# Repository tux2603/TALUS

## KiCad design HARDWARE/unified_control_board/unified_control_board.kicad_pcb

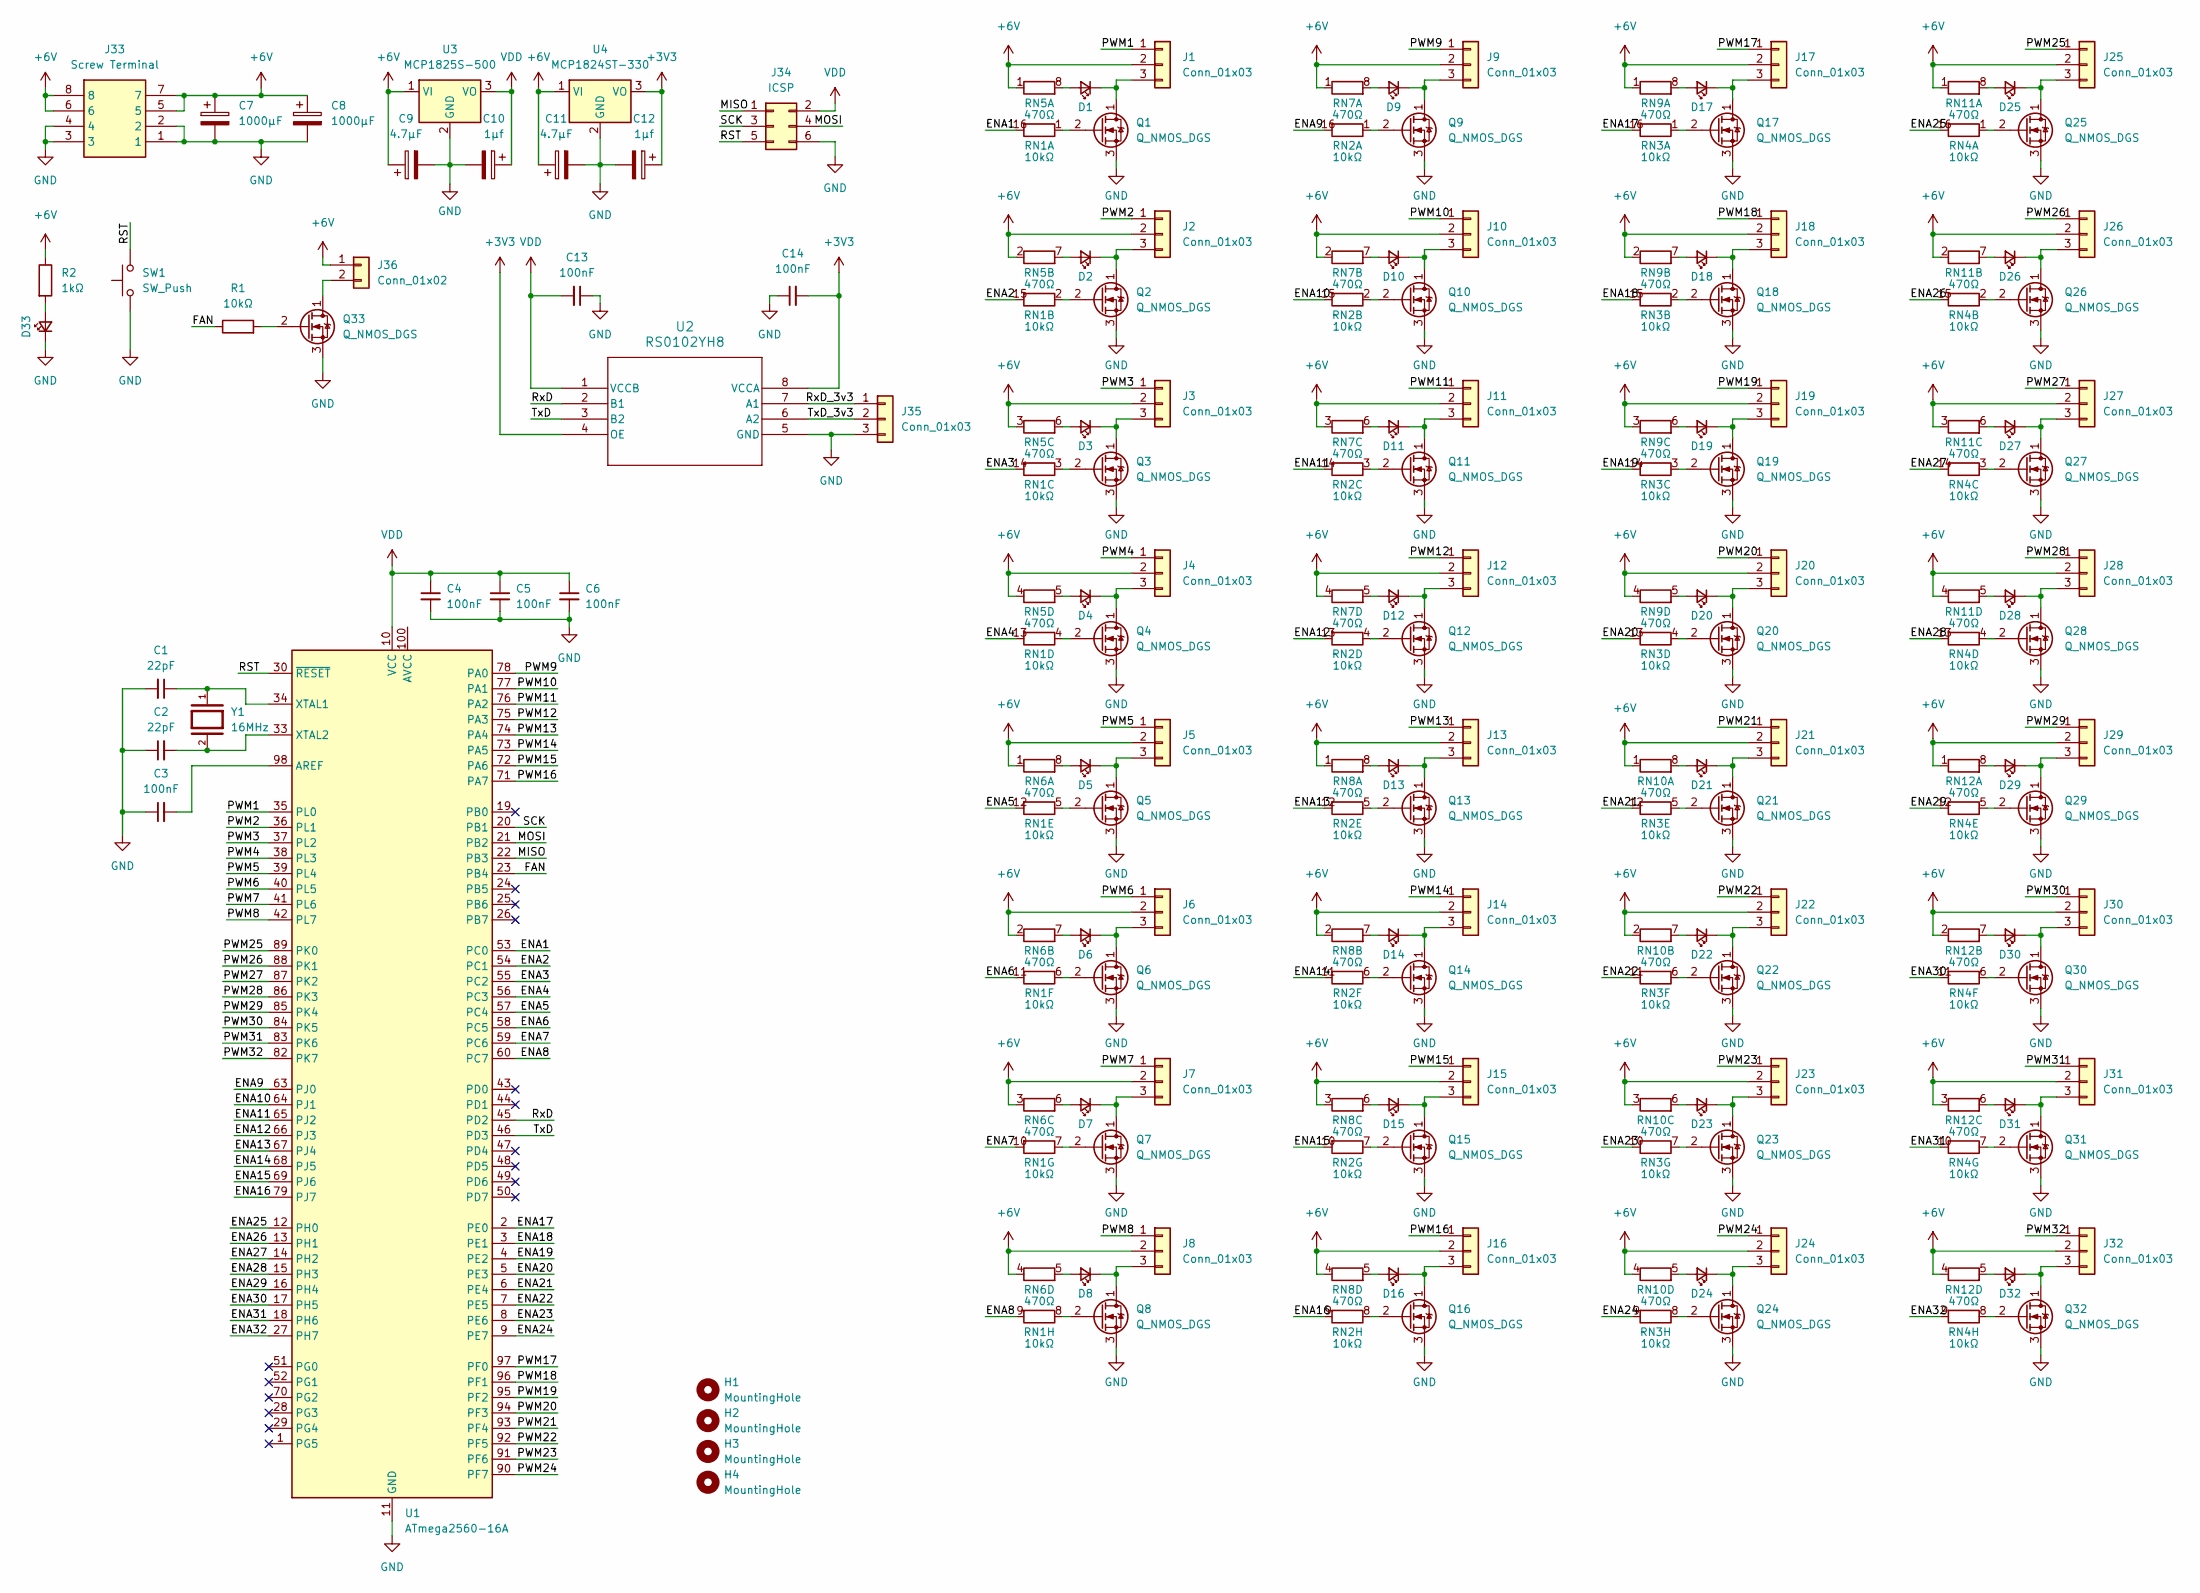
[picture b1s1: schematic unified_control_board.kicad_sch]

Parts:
C1, C2: 22pF; C_0603_1608Metric
C3, C4, C5, C6, C13, C14: 100nF; C_0805_2012Metric
C7, C8: 1000µF; CP_Radial_D10.0mm_P5.00mm
C9, C11: 4.7µF; CP_Elec_4x4.5
C10, C12: 1µf; CP_Elec_4x4.5
D1, D2, D3, D4, D5, D6, D7, D8, D9, D10, D11, D12, D13, D14, D15, D16, D17, D18, D19, D20, D21, D22, D23, D24, D25, D26, D27, D28, D29, D30, D31, D32, D33: Red; LED_0805_2012Metric
H1, H2, H3, H4: MountingHole; MountingHole_2.2mm_M2
J1, J2, J3, J4, J5, J6, J7, J8, J9, J10, J11, J12, J13, J14, J15, J16, J17, J18, J19, J20, J21, J22, J23, J24, J25, J26, J27, J28, J29, J30, J31, J32, J35: Conn_01x03; PinHeader_1x03_P2.54mm_Vertical
J33: Screw Terminal; 399200302; Mouser Part Number 538-39920-0302
J34: ICSP; PinHeader_2x03_P2.54mm_Vertical
J36: Conn_01x02; PinHeader_1x02_P2.54mm_Vertical
Q1, Q2, Q3, Q4, Q5, Q6, Q7, Q8, Q9, Q10, Q11, Q12, Q13, Q14, Q15, Q16, Q17, Q18, Q19, Q20, Q21, Q22, Q23, Q24, Q25, Q26, Q27, Q28, Q29, Q30, Q31, Q32, Q33: Q_NMOS_DGS; SOIC-8_3.9x4.9mm_P1.27mm
R1: 10kΩ; R_0805_2012Metric
R2: 1kΩ; R_0805_2012Metric
RN1, RN2, RN3, RN4: 10kΩ; R_Array_Convex_8x0602
RN5, RN6, RN7, RN8, RN9, RN10, RN11, RN12: 470Ω; R_Array_Convex_4x0603
SW1: SW_Push; SW_PTS647SM38SMTR2LFS_CNK
U1: ATmega2560-16A; TQFP-100_14x14mm_P0.5mm
U2: RS0102YH8; SOT-8-RS0102YH8_JRT
U3: MCP1825S-500; SOT-223-3_TabPin2
U4: MCP1824ST-330; SOT-223-3_TabPin2
Y1: 16MHz; CRYSTAL_HC49SDLF_FXT; PARTREV 11.15.2016; DigiKey_Part_Number 535-9875-2-ND

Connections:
+3V3: C12.1, C14.2, U2.4 (OE), U2.8 (VCCA), U4.3 (VO)
+6V: C7.1, C8.1, C9.1, C11.1, J1.2, J2.2, J3.2, J4.2, J5.2, J6.2, J7.2, J8.2, J9.2, J10.2, J11.2, J12.2, J13.2, J14.2, J15.2, J16.2, J17.2, J18.2, J19.2, J20.2, J21.2, J22.2, J23.2, J24.2, J25.2, J26.2, J27.2, J28.2, J29.2, J30.2, J31.2, J32.2, J33.5, J33.6, J33.7, J33.8, J36.1, R2.1, RN5.1 (R1.1), RN5.2 (R2.1), RN5.3 (R3.1), RN5.4 (R4.1), RN6.1 (R1.1), RN6.2 (R2.1), RN6.3 (R3.1), RN6.4 (R4.1), RN7.1 (R1.1), RN7.2 (R2.1), RN7.3 (R3.1), RN7.4 (R4.1), RN8.1 (R1.1), RN8.2 (R2.1), RN8.3 (R3.1), RN8.4 (R4.1), RN9.1 (R1.1), RN9.2 (R2.1), RN9.3 (R3.1), RN9.4 (R4.1), RN10.1 (R1.1), RN10.2 (R2.1), RN10.3 (R3.1), RN10.4 (R4.1), RN11.1 (R1.1), RN11.2 (R2.1), RN11.3 (R3.1), RN11.4 (R4.1), RN12.1 (R1.1), RN12.2 (R2.1), RN12.3 (R3.1), RN12.4 (R4.1), U3.1 (VI), U4.1 (VI)
/ENA1: RN1.16 (R1.2), U1.53 (PC0)
/ENA2: RN1.15 (R2.2), U1.54 (PC1)
/ENA3: RN1.14 (R3.2), U1.55 (PC2)
/ENA4: RN1.13 (R4.2), U1.56 (PC3)
/ENA5: RN1.12 (R5.2), U1.57 (PC4)
/ENA6: RN1.11 (R6.2), U1.58 (PC5)
/ENA7: RN1.10 (R7.2), U1.59 (PC6)
/ENA8: RN1.9 (R8.2), U1.60 (PC7)
/ENA9: RN2.16 (R1.2), U1.63 (PJ0)
/ENA10: RN2.15 (R2.2), U1.64 (PJ1)
/ENA11: RN2.14 (R3.2), U1.65 (PJ2)
/ENA12: RN2.13 (R4.2), U1.66 (PJ3)
/ENA13: RN2.12 (R5.2), U1.67 (PJ4)
/ENA14: RN2.11 (R6.2), U1.68 (PJ5)
/ENA15: RN2.10 (R7.2), U1.69 (PJ6)
/ENA16: RN2.9 (R8.2), U1.79 (PJ7)
/ENA17: RN3.16 (R1.2), U1.2 (PE0)
/ENA18: RN3.15 (R2.2), U1.3 (PE1)
/ENA19: RN3.14 (R3.2), U1.4 (PE2)
/ENA20: RN3.13 (R4.2), U1.5 (PE3)
/ENA21: RN3.12 (R5.2), U1.6 (PE4)
/ENA22: RN3.11 (R6.2), U1.7 (PE5)
/ENA23: RN3.10 (R7.2), U1.8 (PE6)
/ENA24: RN3.9 (R8.2), U1.9 (PE7)
/ENA25: RN4.16 (R1.2), U1.12 (PH0)
/ENA26: RN4.15 (R2.2), U1.13 (PH1)
/ENA27: RN4.14 (R3.2), U1.14 (PH2)
/ENA28: RN4.13 (R4.2), U1.15 (PH3)
/ENA29: RN4.12 (R5.2), U1.16 (PH4)
/ENA30: RN4.11 (R6.2), U1.17 (PH5)
/ENA31: RN4.10 (R7.2), U1.18 (PH6)
/ENA32: RN4.9 (R8.2), U1.27 (PH7)
/FAN: R1.1, U1.23 (PB4)
/MISO: J34.1, U1.22 (PB3)
/MOSI: J34.4, U1.21 (PB2)
/PWM1: J1.1, U1.35 (PL0)
/PWM2: J2.1, U1.36 (PL1)
/PWM3: J3.1, U1.37 (PL2)
/PWM4: J4.1, U1.38 (PL3)
/PWM5: J5.1, U1.39 (PL4)
/PWM6: J6.1, U1.40 (PL5)
/PWM7: J7.1, U1.41 (PL6)
/PWM8: J8.1, U1.42 (PL7)
/PWM9: J9.1, U1.78 (PA0)
/PWM10: J10.1, U1.77 (PA1)
/PWM11: J11.1, U1.76 (PA2)
/PWM12: J12.1, U1.75 (PA3)
/PWM13: J13.1, U1.74 (PA4)
/PWM14: J14.1, U1.73 (PA5)
/PWM15: J15.1, U1.72 (PA6)
/PWM16: J16.1, U1.71 (PA7)
/PWM17: J17.1, U1.97 (PF0)
/PWM18: J18.1, U1.96 (PF1)
/PWM19: J19.1, U1.95 (PF2)
/PWM20: J20.1, U1.94 (PF3)
/PWM21: J21.1, U1.93 (PF4)
/PWM22: J22.1, U1.92 (PF5)
/PWM23: J23.1, U1.91 (PF6)
/PWM24: J24.1, U1.90 (PF7)
/PWM25: J25.1, U1.89 (PK0)
/PWM26: J26.1, U1.88 (PK1)
/PWM27: J27.1, U1.87 (PK2)
/PWM28: J28.1, U1.86 (PK3)
/PWM29: J29.1, U1.85 (PK4)
/PWM30: J30.1, U1.84 (PK5)
/PWM31: J31.1, U1.83 (PK6)
/PWM32: J32.1, U1.82 (PK7)
/RST: J34.5, SW1.2, U1.30 (~RESET)
/RxD: U1.45 (PD2), U2.2 (B1)
/RxD_3v3: J35.1, U2.7 (A1)
/SCK: J34.3, U1.20 (PB1)
/TxD: U1.46 (PD3), U2.3 (B2)
/TxD_3v3: J35.2, U2.6 (A2)
GND: C1.2, C2.1, C3.1, C4.2, C5.2, C6.2, C7.2, C8.2, C9.2, C10.2, C11.2, C12.2, C13.1, C14.1, D33.1 (K), J33.1, J33.2, J33.3, J33.4, J34.6, J35.3, Q1.3 (S), Q2.3 (S), Q3.3 (S), Q4.3 (S), Q5.3 (S), Q6.3 (S), Q7.3 (S), Q8.3 (S), Q9.3 (S), Q10.3 (S), Q11.3 (S), Q12.3 (S), Q13.3 (S), Q14.3 (S), Q15.3 (S), Q16.3 (S), Q17.3 (S), Q18.3 (S), Q19.3 (S), Q20.3 (S), Q21.3 (S), Q22.3 (S), Q23.3 (S), Q24.3 (S), Q25.3 (S), Q26.3 (S), Q27.3 (S), Q28.3 (S), Q29.3 (S), Q30.3 (S), Q31.3 (S), Q32.3 (S), Q33.3 (S), SW1.1, U1.11 (GND), U1.32 (GND), U1.62 (GND), U1.81 (GND), U1.99 (GND), U2.5 (GND), U3.2 (GND), U4.2 (GND)
unnamed: D1.2 (A), RN5.8 (R1.2)
unnamed: D1.1 (K), J1.3, Q1.1 (D)
unnamed: D2.2 (A), RN5.7 (R2.2)
unnamed: D2.1 (K), J2.3, Q2.1 (D)
unnamed: D3.2 (A), RN5.6 (R3.2)
unnamed: D3.1 (K), J3.3, Q3.1 (D)
unnamed: D4.2 (A), RN5.5 (R4.2)
unnamed: D4.1 (K), J4.3, Q4.1 (D)
unnamed: D5.2 (A), RN6.8 (R1.2)
unnamed: D5.1 (K), J5.3, Q5.1 (D)
unnamed: D6.2 (A), RN6.7 (R2.2)
unnamed: D6.1 (K), J6.3, Q6.1 (D)
unnamed: D7.2 (A), RN6.6 (R3.2)
unnamed: D7.1 (K), J7.3, Q7.1 (D)
unnamed: D8.2 (A), RN6.5 (R4.2)
unnamed: D8.1 (K), J8.3, Q8.1 (D)
unnamed: D9.2 (A), RN7.8 (R1.2)
unnamed: D9.1 (K), J9.3, Q9.1 (D)
unnamed: D10.2 (A), RN7.7 (R2.2)
unnamed: D10.1 (K), J10.3, Q10.1 (D)
unnamed: D11.2 (A), RN7.6 (R3.2)
unnamed: D11.1 (K), J11.3, Q11.1 (D)
unnamed: D12.2 (A), RN7.5 (R4.2)
unnamed: D12.1 (K), J12.3, Q12.1 (D)
unnamed: D13.2 (A), RN8.8 (R1.2)
unnamed: D13.1 (K), J13.3, Q13.1 (D)
unnamed: D14.2 (A), RN8.7 (R2.2)
unnamed: D14.1 (K), J14.3, Q14.1 (D)
unnamed: D15.2 (A), RN8.6 (R3.2)
unnamed: D15.1 (K), J15.3, Q15.1 (D)
unnamed: D16.2 (A), RN8.5 (R4.2)
unnamed: D16.1 (K), J16.3, Q16.1 (D)
unnamed: D17.2 (A), RN9.8 (R1.2)
unnamed: D17.1 (K), J17.3, Q17.1 (D)
unnamed: D18.2 (A), RN9.7 (R2.2)
unnamed: D18.1 (K), J18.3, Q18.1 (D)
unnamed: D19.2 (A), RN9.6 (R3.2)
unnamed: D19.1 (K), J19.3, Q19.1 (D)
unnamed: D20.2 (A), RN9.5 (R4.2)
unnamed: D20.1 (K), J20.3, Q20.1 (D)
unnamed: D21.2 (A), RN10.8 (R1.2)
unnamed: D21.1 (K), J21.3, Q21.1 (D)
unnamed: D22.2 (A), RN10.7 (R2.2)
unnamed: D22.1 (K), J22.3, Q22.1 (D)
unnamed: D23.2 (A), RN10.6 (R3.2)
unnamed: D23.1 (K), J23.3, Q23.1 (D)
unnamed: D24.2 (A), RN10.5 (R4.2)
unnamed: D24.1 (K), J24.3, Q24.1 (D)
unnamed: D25.2 (A), RN11.8 (R1.2)
unnamed: D25.1 (K), J25.3, Q25.1 (D)
unnamed: D26.2 (A), RN11.7 (R2.2)
unnamed: D26.1 (K), J26.3, Q26.1 (D)
unnamed: D27.2 (A), RN11.6 (R3.2)
unnamed: D27.1 (K), J27.3, Q27.1 (D)
unnamed: D28.2 (A), RN11.5 (R4.2)
unnamed: D28.1 (K), J28.3, Q28.1 (D)
unnamed: D29.2 (A), RN12.8 (R1.2)
unnamed: D29.1 (K), J29.3, Q29.1 (D)
unnamed: D30.2 (A), RN12.7 (R2.2)
unnamed: D30.1 (K), J30.3, Q30.1 (D)
unnamed: D31.2 (A), RN12.6 (R3.2)
unnamed: D31.1 (K), J31.3, Q31.1 (D)
unnamed: D32.2 (A), RN12.5 (R4.2)
unnamed: D32.1 (K), J32.3, Q32.1 (D)
unnamed: D33.2 (A), R2.2
unnamed: J36.2, Q33.1 (D)
unnamed: Q1.2 (G), RN1.1 (R1.1)
unnamed: Q2.2 (G), RN1.2 (R2.1)
unnamed: Q3.2 (G), RN1.3 (R3.1)
unnamed: Q4.2 (G), RN1.4 (R4.1)
unnamed: Q5.2 (G), RN1.5 (R5.1)
unnamed: Q6.2 (G), RN1.6 (R6.1)
unnamed: Q7.2 (G), RN1.7 (R7.1)
unnamed: Q8.2 (G), RN1.8 (R8.1)
unnamed: Q9.2 (G), RN2.1 (R1.1)
unnamed: Q10.2 (G), RN2.2 (R2.1)
unnamed: Q11.2 (G), RN2.3 (R3.1)
unnamed: Q12.2 (G), RN2.4 (R4.1)
unnamed: Q13.2 (G), RN2.5 (R5.1)
unnamed: Q14.2 (G), RN2.6 (R6.1)
unnamed: Q15.2 (G), RN2.7 (R7.1)
unnamed: Q16.2 (G), RN2.8 (R8.1)
unnamed: Q17.2 (G), RN3.1 (R1.1)
unnamed: Q18.2 (G), RN3.2 (R2.1)
unnamed: Q19.2 (G), RN3.3 (R3.1)
unnamed: Q20.2 (G), RN3.4 (R4.1)
unnamed: Q21.2 (G), RN3.5 (R5.1)
unnamed: Q22.2 (G), RN3.6 (R6.1)
unnamed: Q23.2 (G), RN3.7 (R7.1)
unnamed: Q24.2 (G), RN3.8 (R8.1)
unnamed: Q25.2 (G), RN4.1 (R1.1)
unnamed: Q26.2 (G), RN4.2 (R2.1)
unnamed: Q27.2 (G), RN4.3 (R3.1)
unnamed: Q28.2 (G), RN4.4 (R4.1)
unnamed: Q29.2 (G), RN4.5 (R5.1)
unnamed: Q30.2 (G), RN4.6 (R6.1)
unnamed: Q31.2 (G), RN4.7 (R7.1)
unnamed: Q32.2 (G), RN4.8 (R8.1)
unnamed: Q33.2 (G), R1.2
unnamed: C3.2, U1.98 (AREF)
unnamed: C1.1, U1.34 (XTAL1), Y1.1
unnamed: C2.2, U1.33 (XTAL2), Y1.2
VDD: C4.1, C5.1, C6.1, C10.1, C13.2, J34.2, U1.10 (VCC), U1.31 (VCC), U1.61 (VCC), U1.80 (VCC), U2.1 (VCCB), U3.3 (VO)

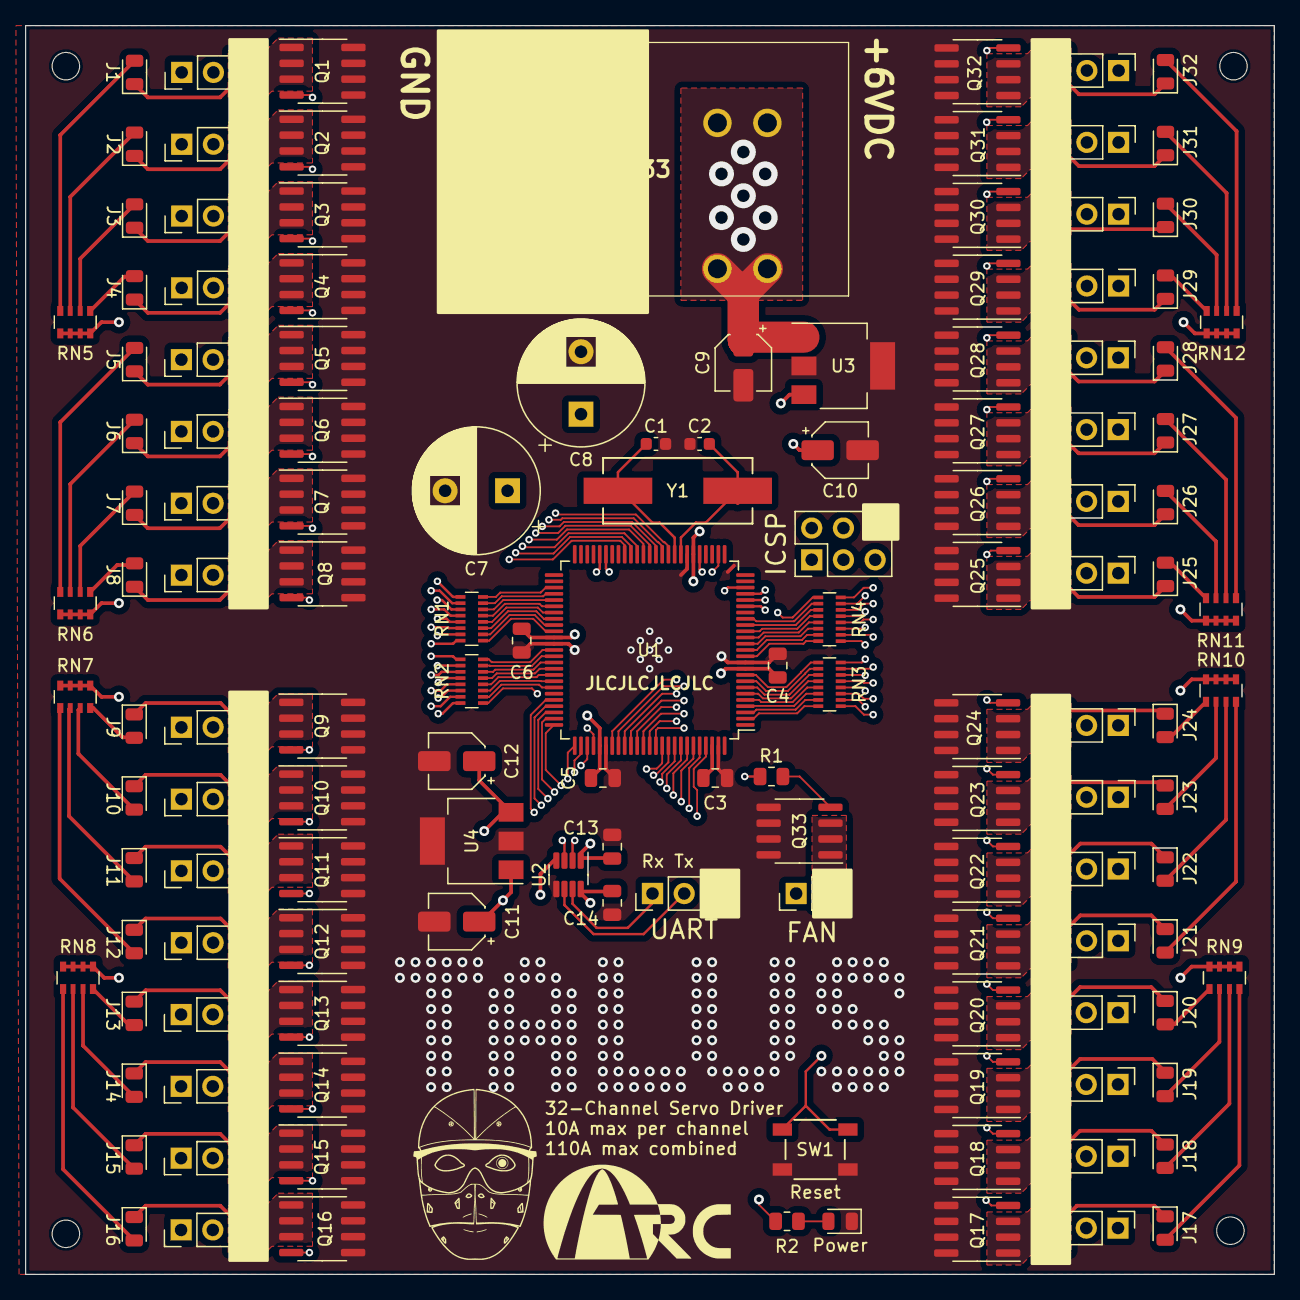
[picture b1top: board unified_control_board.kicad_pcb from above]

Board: 4 copper layers, 100.0 x 100.0 mm, 140 parts (0 on the bottom side), 179 nets.

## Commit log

2023-09-06 Non-routed four layer board
2023-09-07 Routed PCB
2023-09-08 v1.0 of unified control board
2023-09-08 Actually v1 now, forgot to save earlier
